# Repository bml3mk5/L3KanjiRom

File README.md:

# Kanji ROM Card for HITACHI BASIC MASTER LEVEL3

This is my original Kanji ROM Card for HITACHI BASIC MASTER LEVEL3.

## Used Tools

* KiCAD Version 5

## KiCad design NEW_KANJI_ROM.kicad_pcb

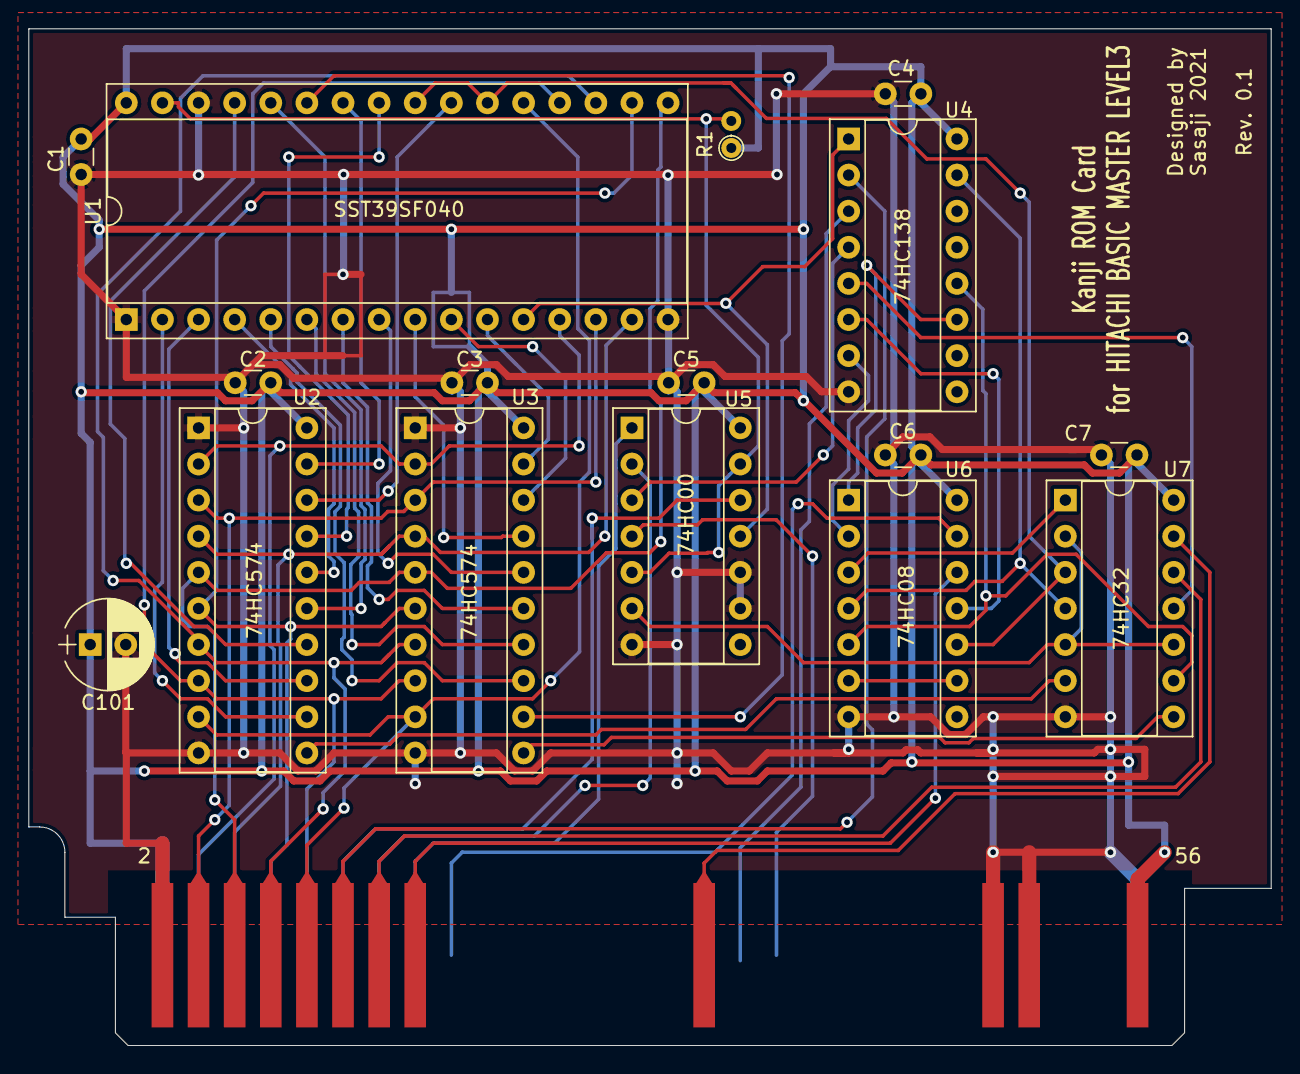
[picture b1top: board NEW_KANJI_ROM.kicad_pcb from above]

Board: 2 copper layers, 87.4 x 71.5 mm, 17 parts (0 on the bottom side), 51 nets.

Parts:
C1, C2, C3, C4, C5, C6, C7: 0.1u; C_Disc_D3.0mm_W1.6mm_P2.50mm
C101: 100u; CP_Radial_D6.3mm_P2.50mm
J1: Conn_02x28_Odd_Even; CardEdge56
R1: 4.7K; R_Axial_DIN0204_L3.6mm_D1.6mm_P1.90mm_Vertical
U1: SST39SF040; DIP-32_W15.24mm_Socket
U2, U3: 74HC574; DIP-20_W7.62mm_Socket
U4: 74HC138; DIP-16_W7.62mm_Socket
U5: 74HC00; DIP-14_W7.62mm_Socket
U6: 74HC08; DIP-14_W7.62mm_Socket
U7: 74HC32; DIP-14_W7.62mm_Socket

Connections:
/A0: J1.11, U5.12
/A1: J1.12, U4.2
/A2: J1.13, U5.2
/A3: J1.14, U7.12
/A4: J1.15, U5.1
/A5: J1.16, U6.12
/A5_A6: U4.6, U6.11
/A6: J1.17, U6.13
/BA1: U1.11, U3.19
/BA2: U1.10, U3.18
/BA3: U1.9, U3.17
/BA4: U1.8, U3.16
/BA5: U1.7, U3.15
/BA6: U1.6, U3.14
/BA7: U1.5, U3.13
/BA8: U1.27, U3.12
/BA9: U1.26, U2.19
/BA10: U1.23, U2.18
/BA11: U1.25, U2.17
/BA12: U1.4, U2.16
/BA13: U1.28, U2.15
/BA14: U1.29, U2.14
/BA15: U1.3, U2.13
/BA16: U1.2, U2.12
/BD0: J1.3, U1.13, U2.2, U3.2
/BD1: J1.4, U1.14, U2.3, U3.3
/BD2: J1.5, U1.15, U2.4, U3.4
/BD3: J1.6, U1.17, U2.5, U3.5
/BD4: J1.7, U1.18, U2.6, U3.6
/BD5: J1.8, U1.19, U2.7, U3.7
/BD6: J1.9, U1.20, U2.8, U3.8
/BD7: J1.10, U1.21, U2.9, U3.9
/E: J1.35, U5.4
/R~W: J1.33, U4.3
/~A2_A4: U4.4, U5.3
/~AA0: U1.12, U4.1, U5.11
/~ASEL3: U4.5, U7.11
/~BE: U5.6, U7.2, U7.5, U7.10
/~DATA_W: U6.6, U6.9
/~EX_IO: J1.32, U7.13
/~FF75_76_R: U6.3, U7.1
/~FF75_76_RE: U1.22, U1.24, U6.10, U7.3
/~FF75_R: U4.11, U6.1
/~FF75_W: U4.15, U6.4, U7.4
/~FF75_WE: U2.11, U7.6
/~FF76_R: U4.7, U6.2
/~FF76_W: U4.12, U6.5, U7.9
/~FF76_WE: U3.11, U7.8
GND: C1.2, C2.2, C3.2, C4.2, C5.2, C6.2, C7.2, C101.2, J1.2, J1.48, J1.50, J1.55, U1.1, U1.16, U1.30, U2.1, U2.10, U3.1, U3.10, U4.8, U5.7, U5.9, U5.10, U6.7, U7.7
PUR1: R1.2, U1.31, U5.5, U5.13
VCC: C1.1, C2.1, C3.1, C4.1, C5.1, C6.1, C7.1, C101.1, J1.1, J1.56, R1.1, U1.32, U2.20, U3.20, U4.16, U5.14, U6.14, U7.14

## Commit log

2023-03-06 Revision 0.1
